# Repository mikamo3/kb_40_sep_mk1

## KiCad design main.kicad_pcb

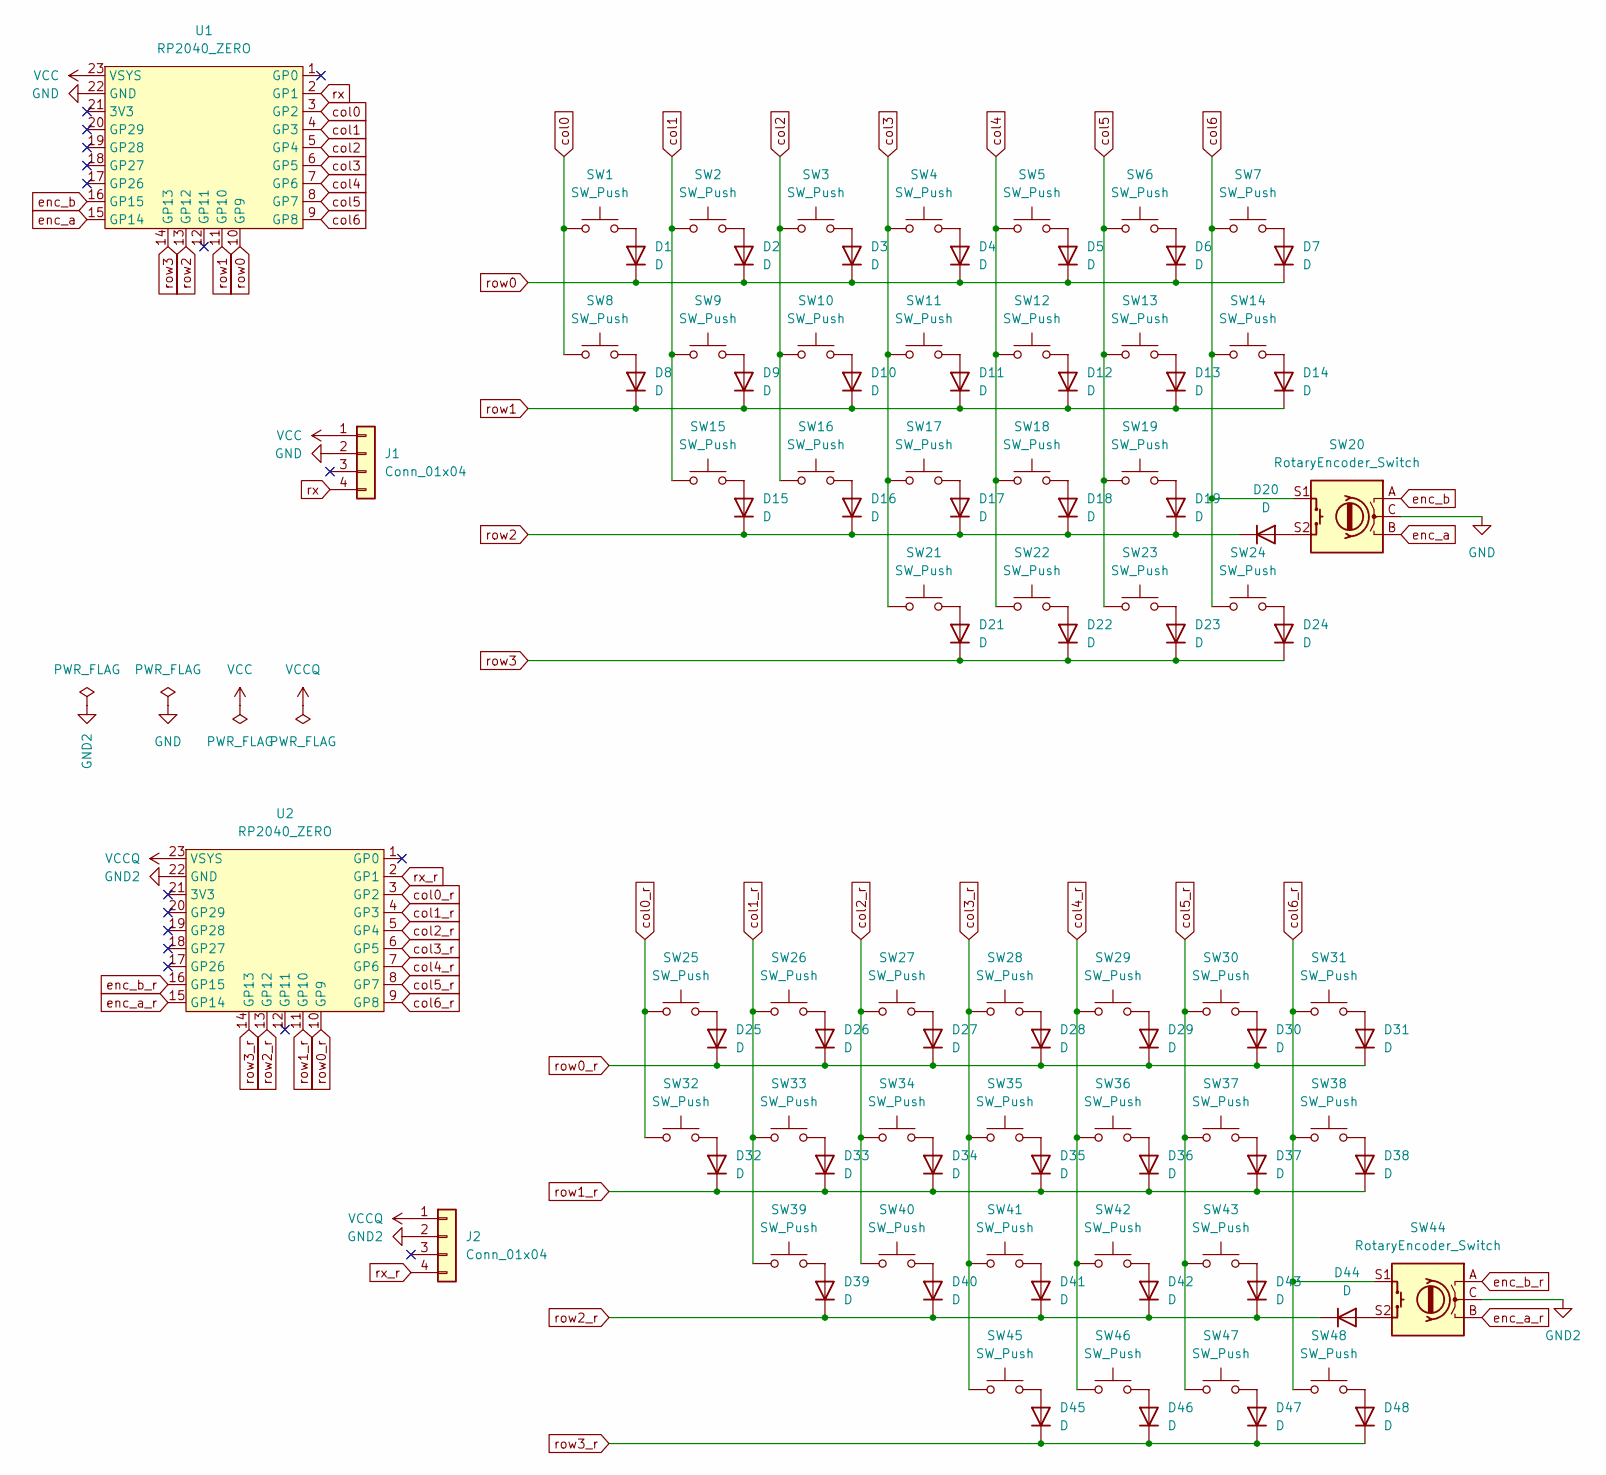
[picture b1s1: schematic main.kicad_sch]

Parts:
D1, D2, D3, D4, D5, D6, D7, D8, D9, D10, D11, D12, D13, D14, D15, D16, D17, D18, D19, D20, D21, D22, D23, D24, D25, D26, D27, D28, D29, D30, D31, D32, D33, D34, D35, D36, D37, D38, D39, D40, D41, D42, D43, D44, D45, D46, D47, D48: D; Diode_SOD123
J1, J2: Conn_01x04; MJ-4PP-9
SW1, SW2, SW3, SW4, SW5, SW6, SW7, SW8, SW9, SW10, SW11, SW12, SW13, SW14, SW15, SW16, SW17, SW18, SW19, SW21, SW22, SW23, SW25, SW26, SW27, SW28, SW29, SW30, SW31, SW32, SW33, SW34, SW35, SW36, SW37, SW38, SW39, SW40, SW41, SW42, SW43, SW45, SW46, SW47: SW_Push; SW_CherryMX_Hotswap_1.00u
SW20, SW44: RotaryEncoder_Switch; RotaryEncoder_EC11
SW24, SW48: SW_Push; SW_CherryMX_Hotswap_1.50u
U1, U2: RP2040_ZERO; RP2040-ZERO_SMD

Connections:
GND: J1.2, SW20.C, U1.22 (GND)
GND2: J2.2, SW44.C, U2.22 (GND)
unnamed: D1.2 (A), SW1.2
unnamed: D2.2 (A), SW2.2
unnamed: D3.2 (A), SW3.2
unnamed: D4.2 (A), SW4.2
unnamed: D5.2 (A), SW5.2
unnamed: D6.2 (A), SW6.2
unnamed: D7.2 (A), SW7.2
unnamed: D8.2 (A), SW8.2
unnamed: D9.2 (A), SW9.2
unnamed: D10.2 (A), SW10.2
unnamed: D11.2 (A), SW11.2
unnamed: D12.2 (A), SW12.2
unnamed: D13.2 (A), SW13.2
unnamed: D14.2 (A), SW14.2
unnamed: D15.2 (A), SW15.2
unnamed: D16.2 (A), SW16.2
unnamed: D17.2 (A), SW17.2
unnamed: D18.2 (A), SW18.2
unnamed: D19.2 (A), SW19.2
unnamed: D20.2 (A), SW20.S2
unnamed: D21.2 (A), SW21.2
unnamed: D22.2 (A), SW22.2
unnamed: D23.2 (A), SW23.2
unnamed: D24.2 (A), SW24.2
unnamed: D25.2 (A), SW25.2
unnamed: D26.2 (A), SW26.2
unnamed: D27.2 (A), SW27.2
unnamed: D28.2 (A), SW28.2
unnamed: D29.2 (A), SW29.2
unnamed: D30.2 (A), SW30.2
unnamed: D31.2 (A), SW31.2
unnamed: D32.2 (A), SW32.2
unnamed: D33.2 (A), SW33.2
unnamed: D34.2 (A), SW34.2
unnamed: D35.2 (A), SW35.2
unnamed: D36.2 (A), SW36.2
unnamed: D37.2 (A), SW37.2
unnamed: D38.2 (A), SW38.2
unnamed: D39.2 (A), SW39.2
unnamed: D40.2 (A), SW40.2
unnamed: D41.2 (A), SW41.2
unnamed: D42.2 (A), SW42.2
unnamed: D43.2 (A), SW43.2
unnamed: D44.2 (A), SW44.S2
unnamed: D45.2 (A), SW45.2
unnamed: D46.2 (A), SW46.2
unnamed: D47.2 (A), SW47.2
unnamed: D48.2 (A), SW48.2
VCC: J1.1, U1.23 (VSYS)
VCCQ: J2.1, U2.23 (VSYS)
col0: SW1.1, SW8.1, U1.3 (GP2)
col0_r: SW25.1, SW32.1, U2.3 (GP2)
col1: SW2.1, SW9.1, SW15.1, U1.4 (GP3)
col1_r: SW26.1, SW33.1, SW39.1, U2.4 (GP3)
col2: SW3.1, SW10.1, SW16.1, U1.5 (GP4)
col2_r: SW27.1, SW34.1, SW40.1, U2.5 (GP4)
col3: SW4.1, SW11.1, SW17.1, SW21.1, U1.6 (GP5)
col3_r: SW28.1, SW35.1, SW41.1, SW45.1, U2.6 (GP5)
col4: SW5.1, SW12.1, SW18.1, SW22.1, U1.7 (GP6)
col4_r: SW29.1, SW36.1, SW42.1, SW46.1, U2.7 (GP6)
col5: SW6.1, SW13.1, SW19.1, SW23.1, U1.8 (GP7)
col5_r: SW30.1, SW37.1, SW43.1, SW47.1, U2.8 (GP7)
col6: SW7.1, SW14.1, SW20.S1, SW24.1, U1.9 (GP8)
col6_r: SW31.1, SW38.1, SW44.S1, SW48.1, U2.9 (GP8)
enc_a: SW20.B, U1.15 (GP14)
enc_a_r: SW44.B, U2.15 (GP14)
enc_b: SW20.A, U1.16 (GP15)
enc_b_r: SW44.A, U2.16 (GP15)
row0: D1.1 (K), D2.1 (K), D3.1 (K), D4.1 (K), D5.1 (K), D6.1 (K), D7.1 (K), U1.10 (GP9)
row0_r: D25.1 (K), D26.1 (K), D27.1 (K), D28.1 (K), D29.1 (K), D30.1 (K), D31.1 (K), U2.10 (GP9)
row1: D8.1 (K), D9.1 (K), D10.1 (K), D11.1 (K), D12.1 (K), D13.1 (K), D14.1 (K), U1.11 (GP10)
row1_r: D32.1 (K), D33.1 (K), D34.1 (K), D35.1 (K), D36.1 (K), D37.1 (K), D38.1 (K), U2.11 (GP10)
row2: D15.1 (K), D16.1 (K), D17.1 (K), D18.1 (K), D19.1 (K), D20.1 (K), U1.13 (GP12)
row2_r: D39.1 (K), D40.1 (K), D41.1 (K), D42.1 (K), D43.1 (K), D44.1 (K), U2.13 (GP12)
row3: D21.1 (K), D22.1 (K), D23.1 (K), D24.1 (K), U1.14 (GP13)
row3_r: D45.1 (K), D46.1 (K), D47.1 (K), D48.1 (K), U2.14 (GP13)
rx: J1.4, U1.2 (GP1)
rx_r: J2.4, U2.2 (GP1)

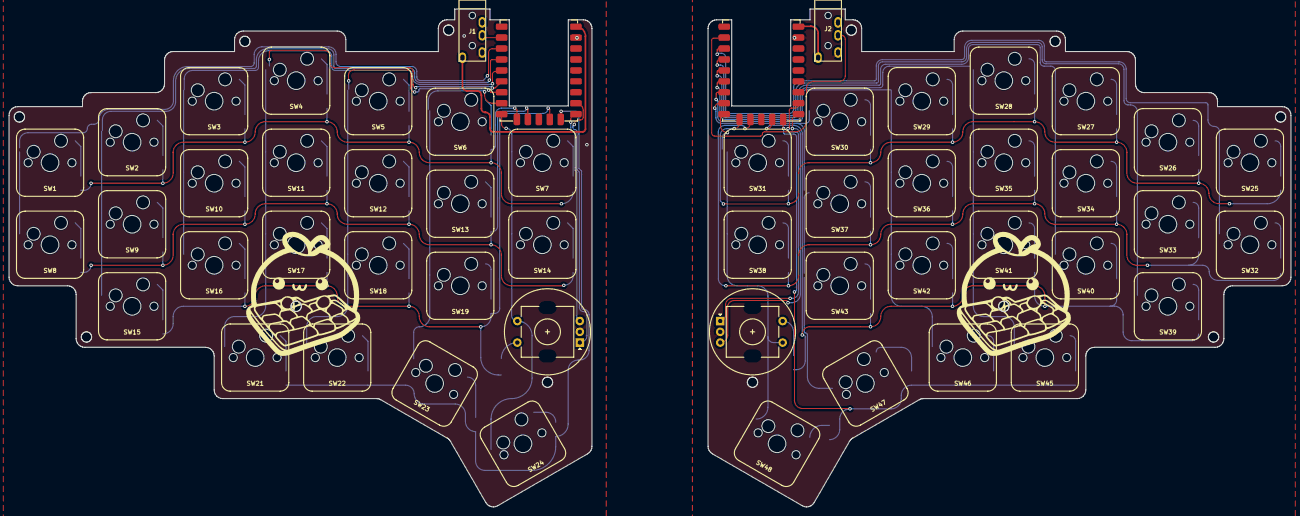
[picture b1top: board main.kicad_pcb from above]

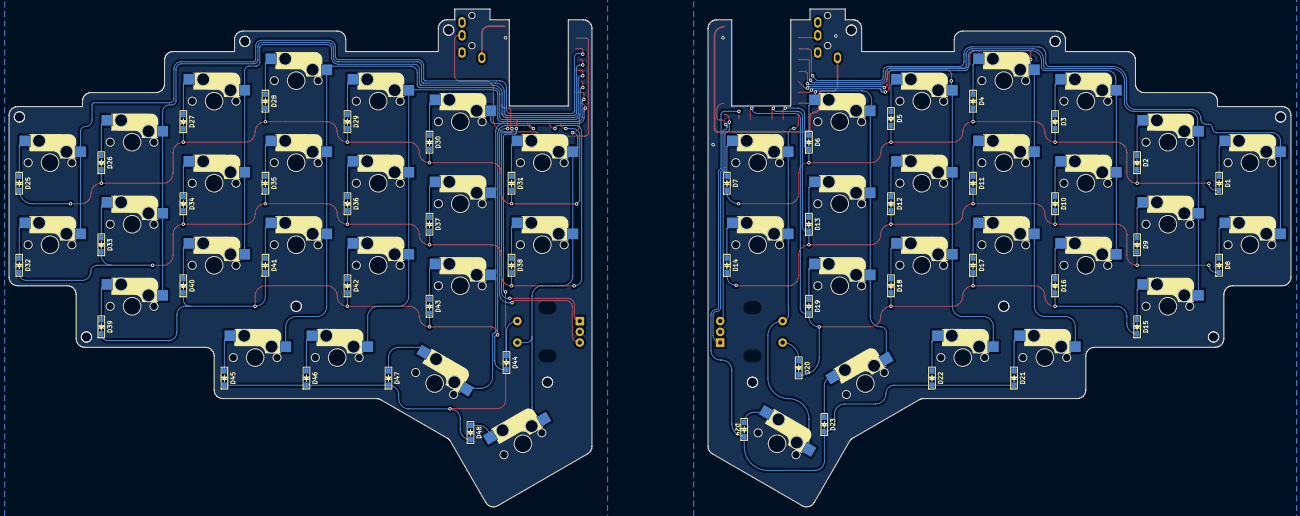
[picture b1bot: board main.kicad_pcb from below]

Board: 2 copper layers, 297.6 x 115.6 mm, 100 parts (48 on the bottom side), 80 nets.

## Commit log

2023-08-15 Create LICENSE
2023-08-15 :sparkles: (layout) add
2023-08-16 :wrench: (gitignore) add
2023-08-17 :construction: (all) wip
2023-08-31 :heavy_plus_sign: (add Keebio-Parts)
2023-08-31 :construction: (main)
2023-08-31 :heavy_plus_sign: (wip)
2023-09-20 :construction:
2023-09-20 :arrow_up: (lib) update submodule
2023-10-15 :sparkles: (all) PCB assembly is complete
2023-10-17 Add keymap
2023-10-18 :sparkles: (keymap) reconfigure
2023-10-25 :bug: (layout) fix
2023-12-18 :sparkles: (keymap) add
2023-12-20 :construction: (pcb) fix
2023-12-24 :construction: (pcb) write route done.
2024-01-03 :bug: (pcb) reconfigure pcb
2024-02-07 :sparkles: (all) ready for manufacturing
